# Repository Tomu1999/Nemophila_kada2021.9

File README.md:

# Nemophila_kada2021.9

2021年度秋加太共同実験のネモフィラ号において自分の担当分をUPする。

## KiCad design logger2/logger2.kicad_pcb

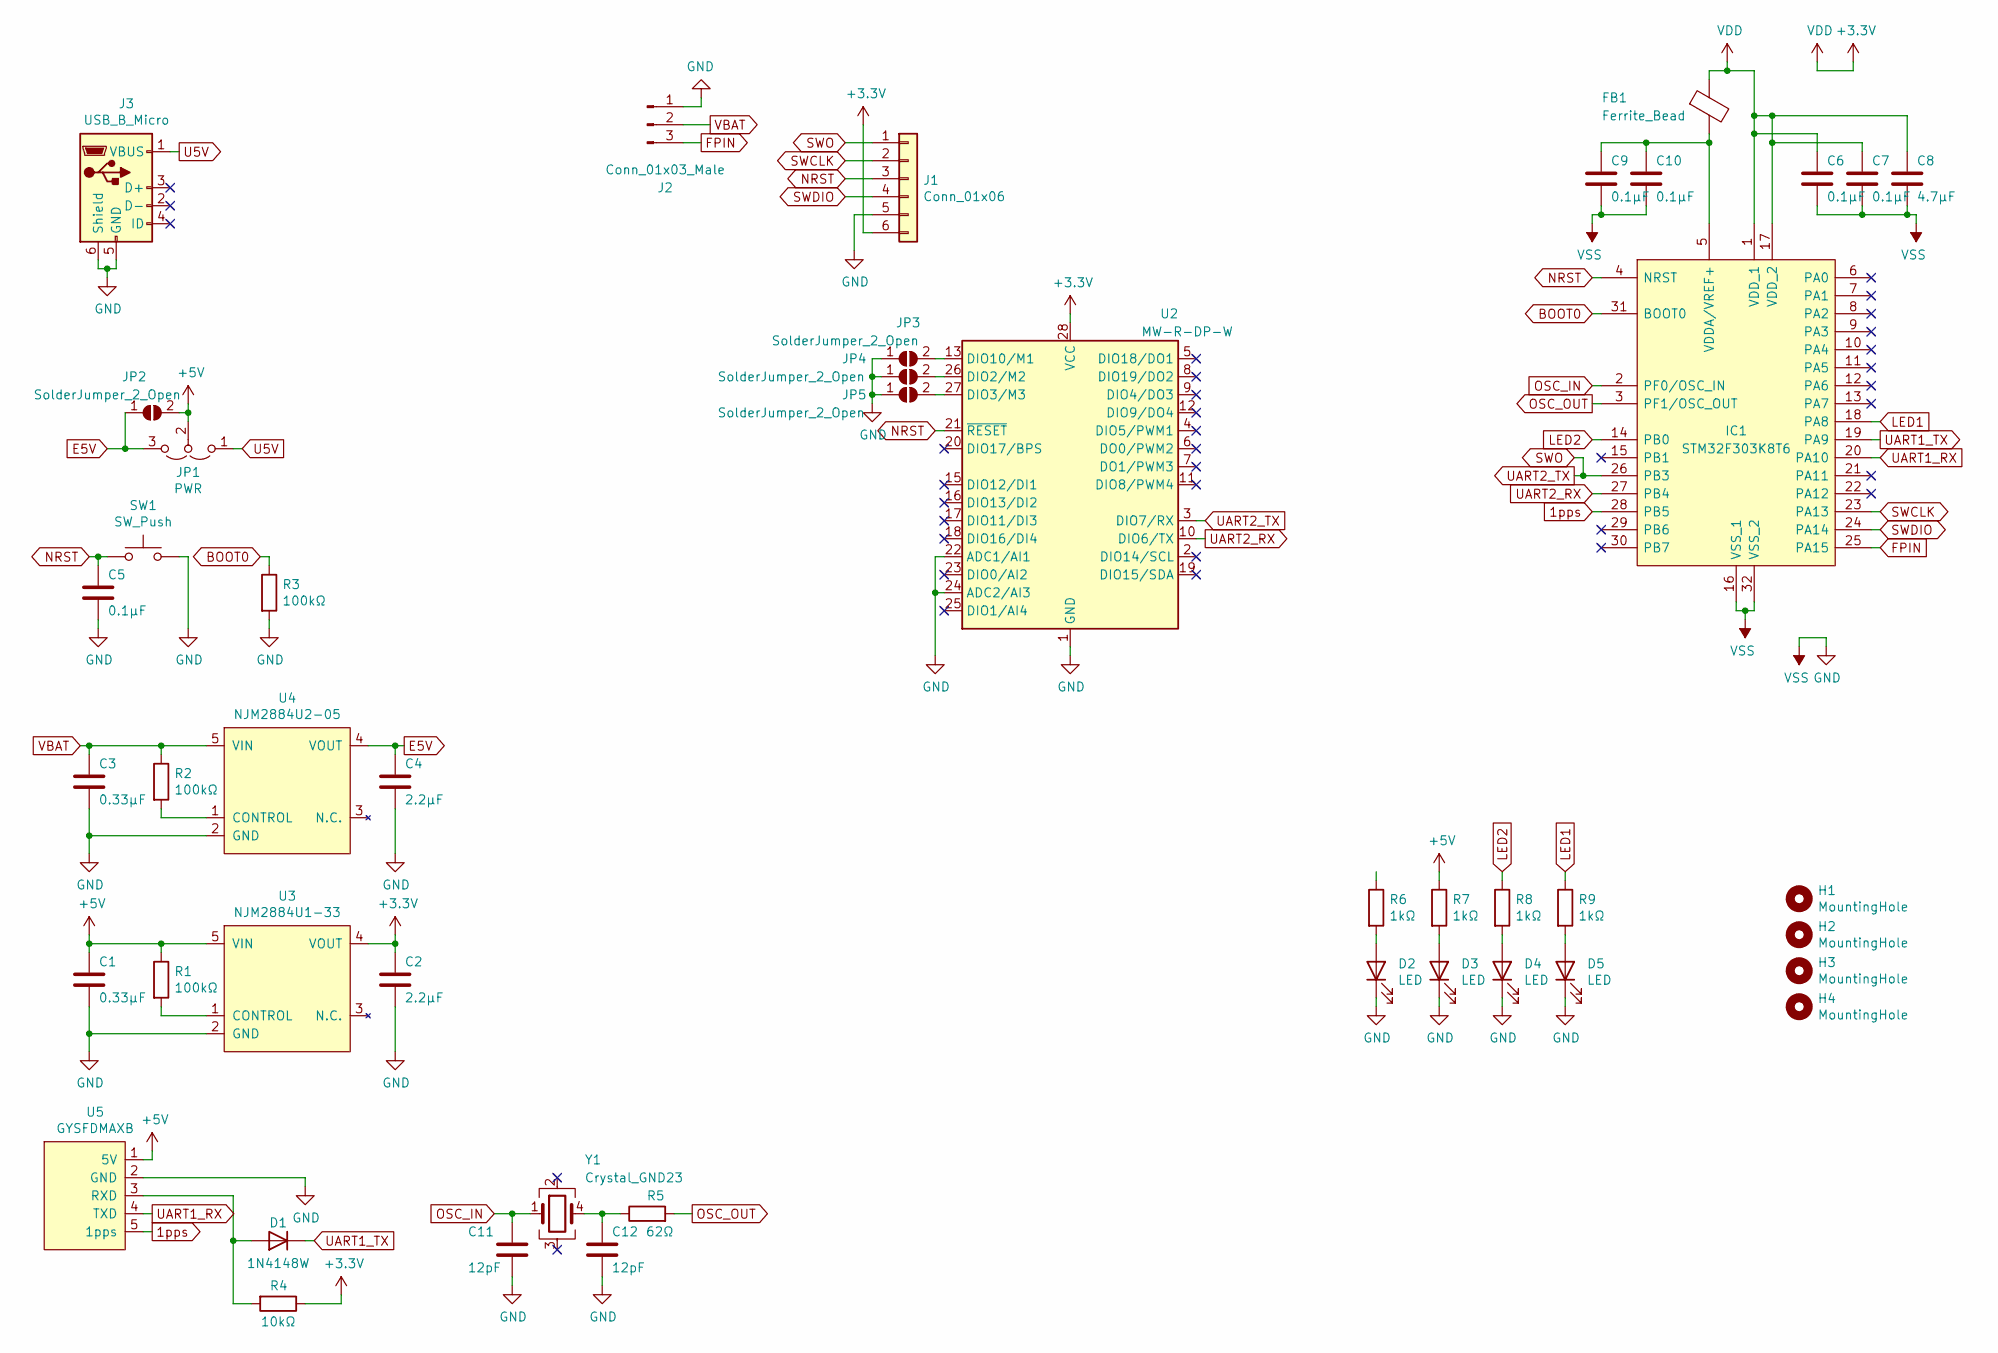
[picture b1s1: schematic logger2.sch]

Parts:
C1, C3: 0.33μF; C_0603_1608Metric
C2, C4: 2.2μF; C_0603_1608Metric
C5, C6, C7, C9, C10: 0.1μF; C_0603_1608Metric
C8: 4.7μF; C_0603_1608Metric
C11, C12: 12pF; C_0603_1608Metric
D1: 1N4148W; D_SOD-123
D2, D3, D4, D5: LED; LED_0603_1608Metric
FB1: Ferrite_Bead; R_0603_1608Metric
H1, H2, H3, H4: MountingHole; MountingHole_3.2mm_M3_Pad_Via
IC1: STM32F303K8T6; QFP80P900X900X160-32N; Manufacturer_Part_Number STM32F303K8T6; Mouser Part Number 511-STM32F303K8T6
J1: Conn_01x06; PinHeader_1x06_P2.54mm_Vertical
J2: Conn_01x03_Male; Hirose_DF1E_DF1E-3P-2.5DS_1x03_P2.5mm_Horizontal
J3: USB_B_Micro; ZX62B5PA33
JP1: PWR; PinSocket_1x03_P2.54mm_Vertical
JP2, JP3, JP4, JP5: SolderJumper_2_Open; SolderJumper-2_P1.3mm_Open_TrianglePad1.0x1.5mm
R1, R2, R3: 100kΩ; R_0603_1608Metric
R4: 10kΩ; R_0603_1608Metric
R5: 62Ω; R_0603_1608Metric
R6, R7, R8, R9: 1kΩ; R_0603_1608Metric
SW1: SW_Push; TVAF06-A020B-R
U2: MW-R-DP-W; DIP-28_W15.24mm
U3: NJM2884U1-33; SOT-89-5
U4: NJM2884U2-05; SOT-89-5
U5: GYSFDMAXB; PinSocket_1x05_P2.54mm_Horizontal
Y1: Crystal_GND23; Crystal_SMD_SeikoEpson_MA506-4Pin_12.7x5.1mm

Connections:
1pps: IC1.28 (PB5), U5.5 (1pps)
+3V3: C2.1, C6.1, C7.1, C8.1, FB1.1, IC1.1 (VDD_1), IC1.17 (VDD_2), J1.6, R4.1, U2.28 (VCC), U3.4 (VOUT)
+5V: C1.1, JP1.2 (C), JP2.2 (B), R1.1, R7.1, U3.5 (VIN), U5.1 (5V)
BOOT0: IC1.31 (BOOT0), R3.1
E5V: C4.1, JP1.3 (B), JP2.1 (A), U4.4 (VOUT)
FPIN: IC1.25 (PA15), J2.3
GND: C1.2, C2.2, C3.2, C4.2, C5.2, C6.2, C7.2, C8.2, C9.2, C10.2, C11.2, C12.2, D2.1 (K), D3.1 (K), D4.1 (K), D5.1 (K), IC1.16 (VSS_1), IC1.32 (VSS_2), J1.5, J2.1, J3.5 (GND), J3.6 (Shield), JP3.1 (A), JP4.1 (A), JP5.1 (A), R3.2, SW1.2, U2.1 (GND), U2.14 (GND), U2.22 (ADC1/AI1), U2.24 (ADC2/AI3), U3.2 (GND), U4.2 (GND), U5.2 (GND)
LED1: IC1.18 (PA8), R9.1
LED2: IC1.14 (PB0), R8.1
NRST: C5.1, IC1.4 (NRST), J1.3, SW1.1, U2.21 (~RESET)
unnamed: C9.1, C10.1, FB1.2, IC1.5 (VDDA/VREF+)
unnamed: C12.1, R5.1, Y1.4
unnamed: D1.2 (A), R4.2, U5.3 (RXD)
unnamed: D2.2 (A), R6.2
unnamed: D3.2 (A), R7.2
unnamed: D4.2 (A), R8.2
unnamed: D5.2 (A), R9.2
unnamed: JP3.2 (B), U2.13 (DIO10/M1)
unnamed: JP4.2 (B), U2.26 (DIO2/M2)
unnamed: JP5.2 (B), U2.27 (DIO3/M3)
unnamed: R1.2, U3.1 (CONTROL)
unnamed: R2.2, U4.1 (CONTROL)
OSC_IN: C11.1, IC1.2 (PF0/OSC_IN), Y1.1
OSC_OUT: IC1.3 (PF1/OSC_OUT), R5.2
SWCLK: IC1.23 (PA13), J1.2
SWDIO: IC1.24 (PA14), J1.4
SWO: IC1.26 (PB3), J1.1, U2.3 (DIO7/RX)
U5V: J3.1 (VBUS), JP1.1 (A)
UART1_RX: IC1.20 (PA10), U5.4 (TXD)
UART1_TX: D1.1 (K), IC1.19 (PA9)
UART2_RX: IC1.27 (PB4), U2.10 (DIO6/TX)
VBAT: C3.1, J2.2, R2.1, U4.5 (VIN)

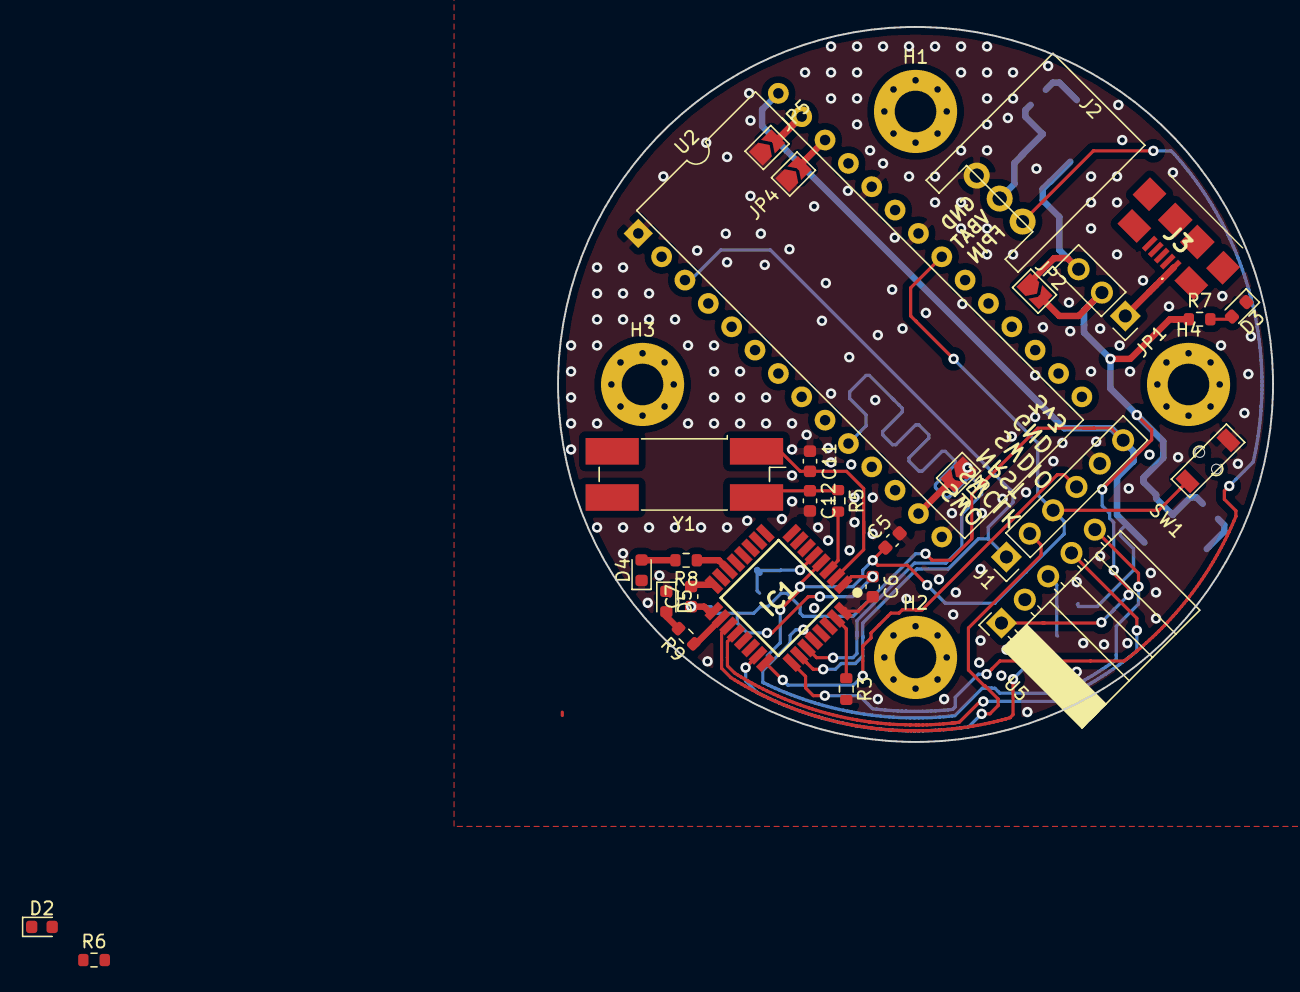
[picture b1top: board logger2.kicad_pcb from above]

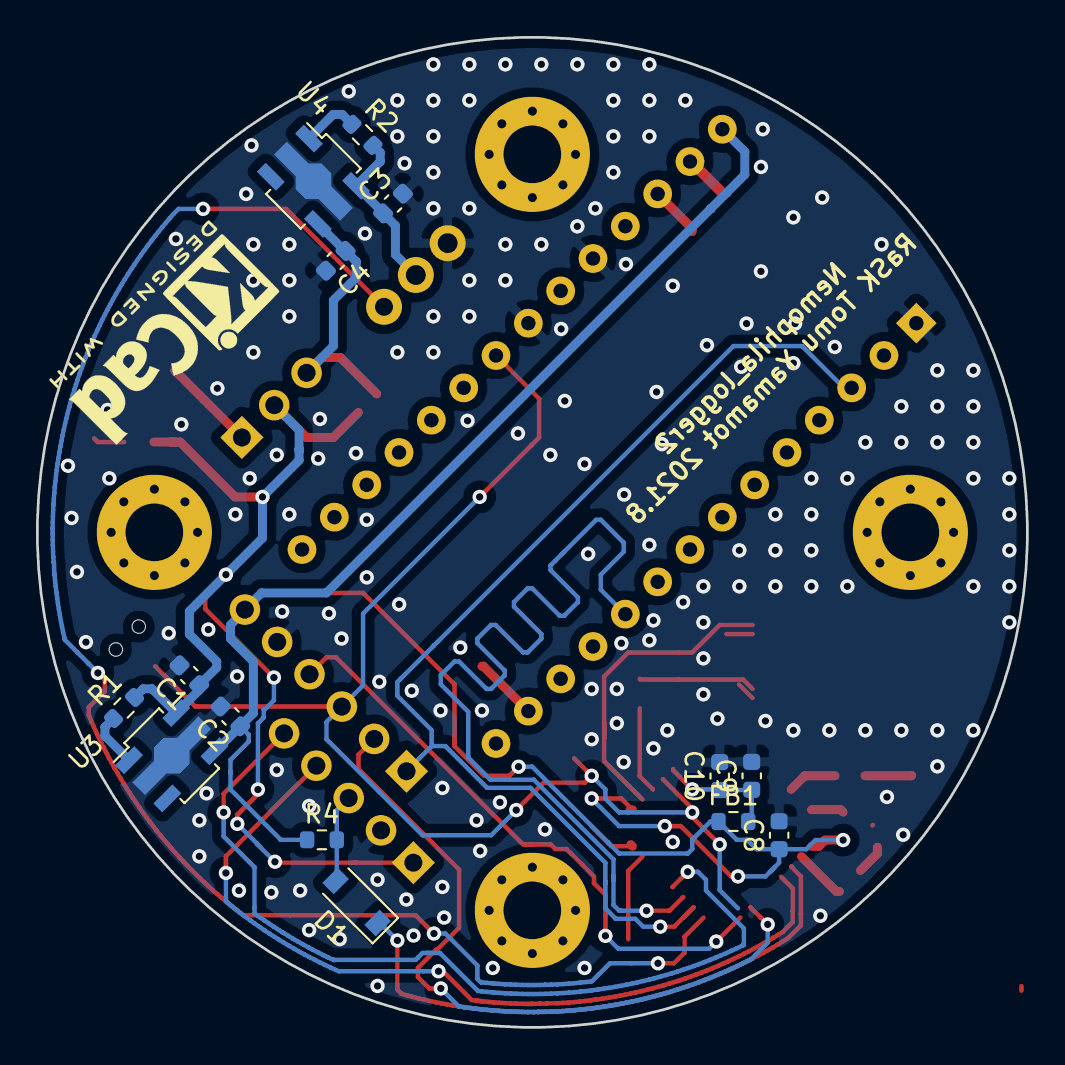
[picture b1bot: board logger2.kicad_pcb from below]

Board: 2 copper layers, 55.0 x 55.0 mm, 46 parts (14 on the bottom side), 32 nets.
